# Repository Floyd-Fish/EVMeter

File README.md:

# Overview
An EV(Exposure Value) Meter measures EV parameters for cameras automatically. Also measures the Color Temperature.Designed to simplify MF controls on Digital or Mechanical DSLRs

## Progress

V2.1 has been updated: Basic functions completed, **but bug exists**.  

## Hardware design
Tools: KiCad  
See dir: Hardware/Kicad_project

## Software design

**History Version**

- V1.0
  - Tools: Clion + STM32CubeMx  
  - MCU: STM32F070F6P6  
  - See dir: Software

- V2.0
  - Tools: Clion + STM32CubeMx
  - MCU: STM32F072CBT6
  - See dir: Software

- V2.1
  - Tools: MDK5 + STM32CubeMx
  - MCU: STM32F072CBT6
  - See dir: Software

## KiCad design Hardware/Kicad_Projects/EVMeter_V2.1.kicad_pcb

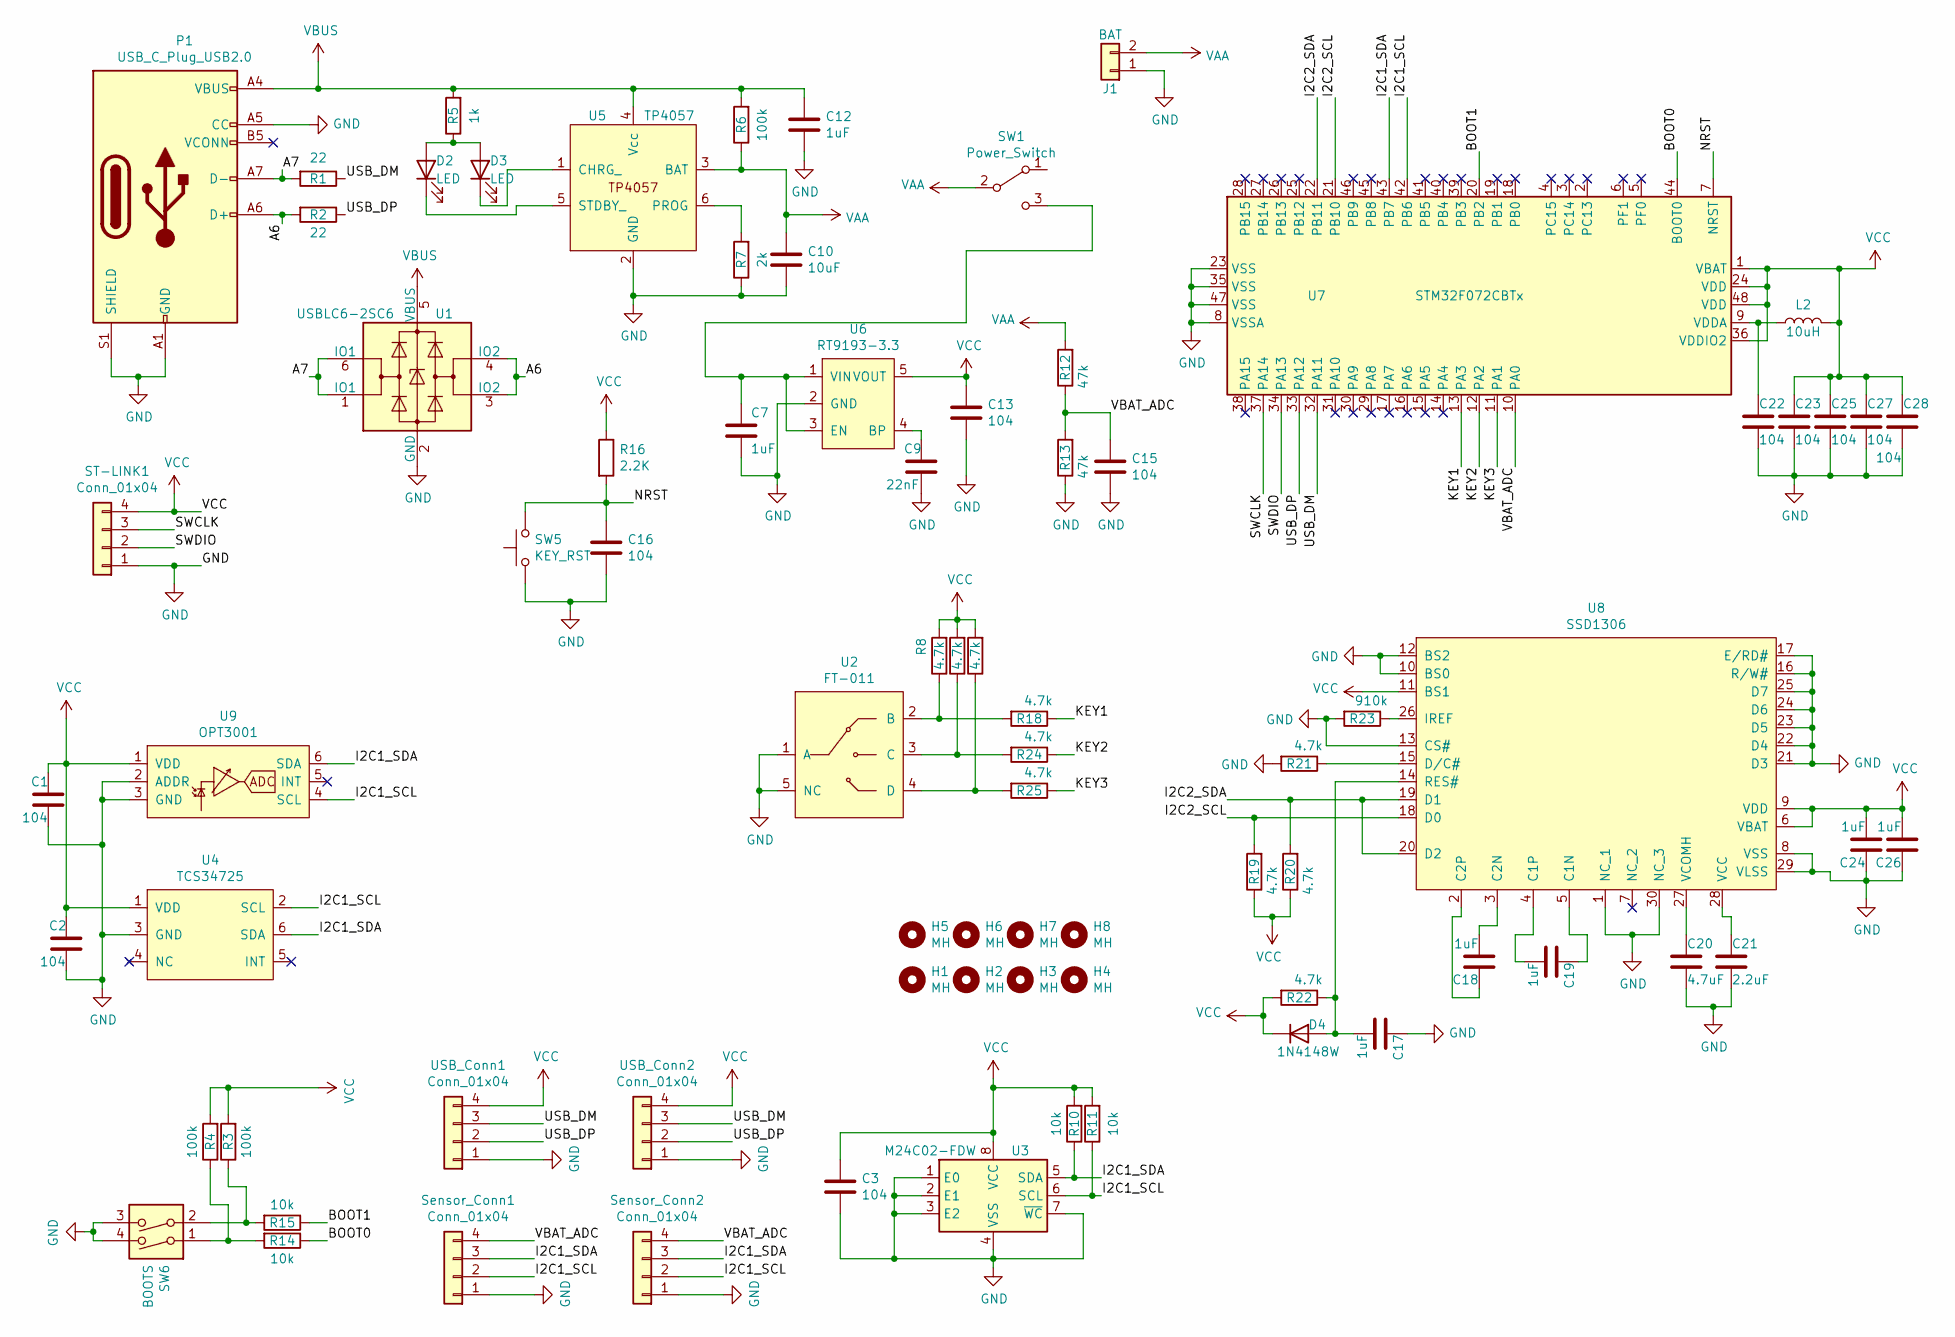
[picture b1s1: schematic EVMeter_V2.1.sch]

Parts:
C1, C2, C3, C13, C15, C16, C22, C23, C25, C27, C28: 104; C_0603_1608Metric
C7, C12, C17, C18, C19, C24, C26: 1uF; C_0603_1608Metric
C9: 22nF; C_0603_1608Metric
C10: 10uF; C_0805_2012Metric
C20: 4.7uF; C_0805_2012Metric
C21: 2.2uF; C_0805_2012Metric
D2, D3: LED; LED_0603_1608Metric_Castellated
D4: 1N4148W; D_SOD-323
H1, H2, H3, H4, H5, H6, H7, H8: MH; MountingHole_2.2mm_M2
J1: BAT; PinSocket_1x02_P2.00mm_Vertical
L2: 10uH; L_0805_2012Metric_Pad1.15x1.40mm_HandSolder
P1: USB_C_Plug_USB2.0; USB_C_Receptacle_HRO_TYPE-C-31-M-12
R1, R2: 22; R_0603_1608Metric
R3, R4, R6: 100k; R_0603_1608Metric
R5: 1k; R_0603_1608Metric
R7: 2k; R_0603_1608Metric
R8, R9, R17, R18, R19, R20, R21, R22, R24, R25: 4.7k; R_0603_1608Metric
R10, R11, R14, R15: 10k; R_0603_1608Metric
R12, R13: 47k; R_0603_1608Metric
R16: 2.2K; R_0603_1608Metric
R23: 910k; R_0603_1608Metric
ST-LINK1: Conn_01x04; Molex_PicoBlade_53261-0471_1x04-1MP_P1.25mm_Horizontal
SW1: Power_Switch; SW_SPDT_CK-JS102011SAQN
SW5: KEY_RST; Panasonic_EVQPUL_EVQPUC
SW6: BOOTS; SW_DIP_SPSTx02_Slide_Yourcee_W5.40mm_P1.27mm
Sensor_Conn1: Conn_01x04; PinHeader_1x04_P2.54mm_Vertical
Sensor_Conn2: Conn_01x04; PinSocket_1x04_P2.54mm_Vertical
U1: USBLC6-2SC6; SOT-23-6
U2: FT-011
U3: M24C02-FDW; SOIC-8_3.9x4.9mm_P1.27mm
U4: TCS34725; TSL2591_DFN6
U5: TP4057; SOT-23-6
U6: RT9193-3.3; SOT-23-5
U7: STM32F072CBTx; LQFP-48_7x7mm_P0.5mm
U8: SSD1306; SSD1306-12864_Alter
U9: OPT3001; USON-6
USB_Conn1: Conn_01x04; PinHeader_1x04_P2.54mm_Vertical
USB_Conn2: Conn_01x04; PinSocket_1x04_P2.54mm_Vertical

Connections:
/A6: P1.A6 (D+), R2.2, U1.3 (IO2), U1.4 (IO2)
/A7: P1.A7 (D-), R1.2, U1.1 (IO1), U1.6 (IO1)
/BOOT0: R14.1, U7.44 (BOOT0)
/BOOT1: R15.1, U7.20 (PB2)
/I2C1_SCL: R11.1, Sensor_Conn1.2, Sensor_Conn2.2, U3.6 (SCL), U4.2 (SCL), U7.42 (PB6), U9.4 (SCL)
/I2C1_SDA: R10.1, Sensor_Conn1.3, Sensor_Conn2.3, U3.5 (SDA), U4.6 (SDA), U7.43 (PB7), U9.6 (SDA)
/I2C2_SCL: R19.2, U7.21 (PB10), U8.18 (D0)
/I2C2_SDA: R20.2, U7.22 (PB11), U8.19 (D1), U8.20 (D2)
/KEY1: R18.1, U7.13 (PA3)
/KEY2: R24.1, U7.12 (PA2)
/KEY3: R25.1, U7.11 (PA1)
/NRST: C16.1, R16.2, SW5.2, U7.7 (NRST)
/SWCLK: ST-LINK1.3, U7.37 (PA14)
/SWDIO: ST-LINK1.2, U7.34 (PA13)
/USB_DM: R1.1, U7.32 (PA11), USB_Conn1.3, USB_Conn2.3
/USB_DP: R2.1, U7.33 (PA12), USB_Conn1.2, USB_Conn2.2
/VBAT_ADC: C15.1, R12.1, R13.2, Sensor_Conn1.4, Sensor_Conn2.4, U7.10 (PA0)
GND: C1.2, C2.2, C3.2, C7.2, C9.2, C10.2, C12.2, C13.2, C15.2, C16.2, C17.1, C20.2, C21.2, C22.2, C23.2, C24.1, C25.2, C26.1, C27.2, C28.2, J1.1, P1.A1 (GND), P1.A5 (CC), P1.A12 (GND), P1.B1 (GND), P1.B12 (GND), P1.S1 (SHIELD), R7.1, R13.1, R21.2, R23.2, ST-LINK1.1, SW5.1, SW6.3, SW6.4, Sensor_Conn1.1, Sensor_Conn2.1, U1.2 (GND), U2.1 (A), U2.5 (NC), U3.1 (E0), U3.2 (E1), U3.3 (E2), U3.4 (VSS), U3.7 (~WC), U4.3 (GND), U5.2 (GND), U6.2 (GND), U7.8 (VSSA), U7.23 (VSS), U7.35 (VSS), U7.47 (VSS), U8.1 (NC_1), U8.8 (VSS), U8.10 (BS0), U8.12 (BS2), U8.13 (CS#), U8.16 (R/W#), U8.17 (E/RD#), U8.21 (D3), U8.22 (D4), U8.23 (D5), U8.24 (D6), U8.25 (D7), U8.29 (VLSS), U8.30 (NC_3), U9.2 (ADDR), U9.3 (GND), USB_Conn1.1, USB_Conn2.1
unnamed: C7.1, SW1.3 (C), U6.1 (VIN), U6.3 (EN)
unnamed: C9.1, U6.4 (BP)
unnamed: C17.2, D4.2 (A), R22.1, U8.14 (RES#)
unnamed: C18.1, U8.2 (C2P)
unnamed: C18.2, U8.3 (C2N)
unnamed: C19.1, U8.5 (C1N)
unnamed: C19.2, U8.4 (C1P)
unnamed: C20.1, U8.27 (VCOMH)
unnamed: C21.1, U8.28 (VCC)
unnamed: C22.1, L2.1, U7.9 (VDDA)
unnamed: D2.1 (K), U5.5 (STDBY_)
unnamed: D2.2 (A), D3.2 (A), R5.1
unnamed: D3.1 (K), U5.1 (CHRG_)
unnamed: R7.2, U5.6 (PROG)
unnamed: R4.1, R14.2, SW6.1
unnamed: R3.1, R15.2, SW6.2
unnamed: R17.1, R25.2, U2.4 (D)
unnamed: R8.1, R18.2, U2.2 (B)
unnamed: R21.1, U8.15 (D/C#)
unnamed: R23.1, U8.26 (IREF)
unnamed: R9.1, R24.2, U2.3 (C)
VAA: C10.1, J1.2, R6.1, R12.2, SW1.2 (B), U5.3 (BAT)
VBUS: C12.1, P1.A4 (VBUS), P1.A9 (VBUS), P1.B4 (VBUS), P1.B9 (VBUS), R5.2, R6.2, U1.5 (VBUS), U5.4 (Vcc)
VCC: C1.1, C2.1, C3.1, C13.1, C23.1, C24.2, C25.1, C26.2, C27.1, C28.1, D4.1 (K), L2.2, R3.2, R4.2, R8.2, R9.2, R10.2, R11.2, R16.1, R17.2, R19.1, R20.1, R22.2, ST-LINK1.4, U3.8 (VCC), U4.1 (VDD), U6.5 (VOUT), U7.1 (VBAT), U7.24 (VDD), U7.36 (VDDIO2), U7.48 (VDD), U8.6 (VBAT), U8.9 (VDD), U8.11 (BS1), U9.1 (VDD), USB_Conn1.4, USB_Conn2.4

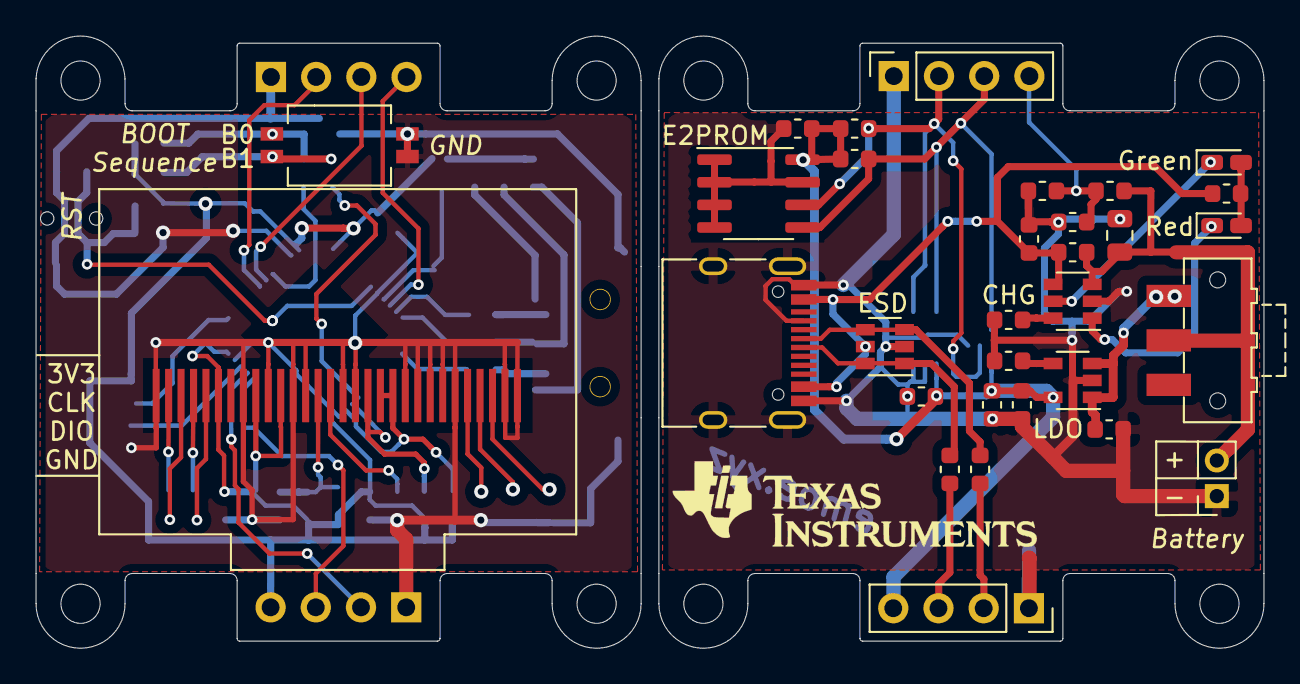
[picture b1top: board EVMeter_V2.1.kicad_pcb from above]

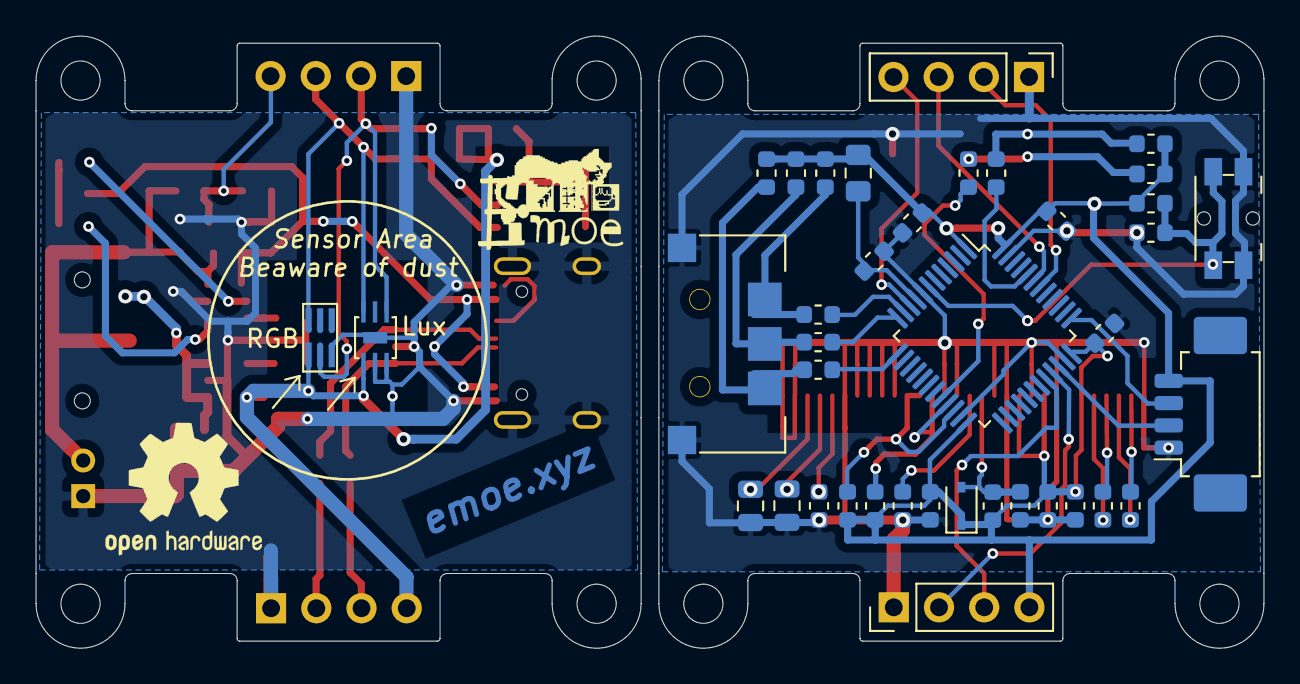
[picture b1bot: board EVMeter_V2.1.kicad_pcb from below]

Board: 2 copper layers, 69.0 x 34.4 mm, 78 parts (39 on the bottom side), 42 nets.

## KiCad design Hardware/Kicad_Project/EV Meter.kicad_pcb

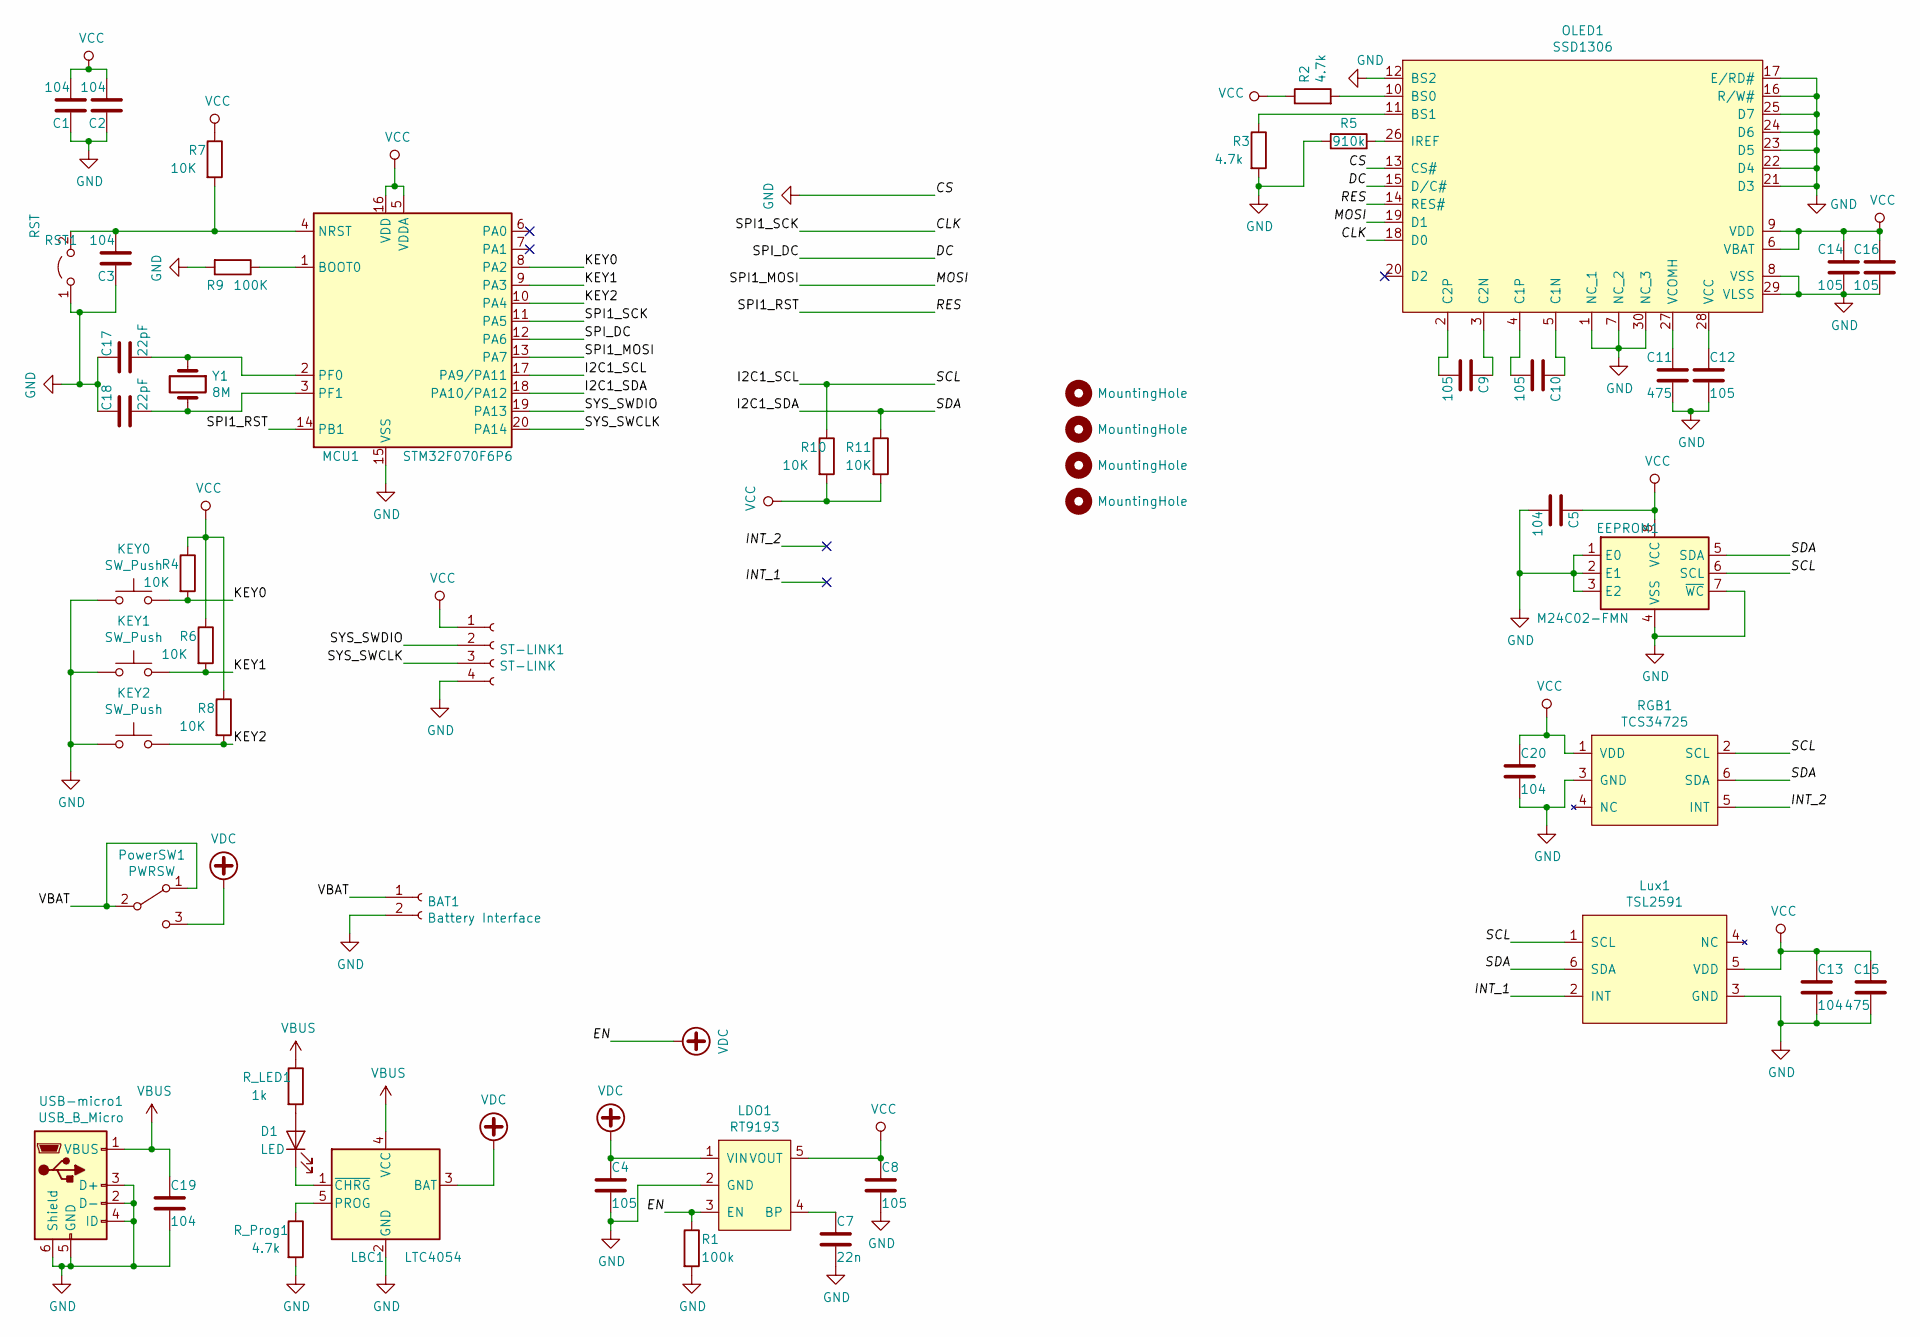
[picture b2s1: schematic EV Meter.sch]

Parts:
BAT1: Battery Interface; PinSocket_1x02_P2.54mm_Vertical
C1, C2, C3, C5, C13, C19, C20: 104; C_0603_1608Metric
C4, C8, C9, C10, C12, C14, C16: 105; C_0603_1608Metric
C7: 22n; C_0603_1608Metric
C11, C15: 475; C_0805_2012Metric
C17, C18: 22pF; C_0603_1608Metric
D1: LED; LED_0603_1608Metric
EEPROM1: M24C02-FMN; SOIC-8_3.9x4.9mm_P1.27mm
H1, H2, H3, H4: MountingHole; MountingHole_2.2mm_M2_DIN965
KEY0, KEY1, KEY2: SW_Push; SW_SPST_TL3305C
LBC1: LTC4054; SOT-23-5
LDO1: RT9193; SOT-23-5
Lux1: TSL2591; TSL2591_DFN6
MCU1: STM32F070F6P6; TSSOP-20_4.4x6.5mm_P0.65mm
OLED1: SSD1306; SSD1306-12864
PowerSW1: PWRSW; SW_SPDT_CK-JS102011SAQN
R1: 100k; R_0603_1608Metric
R2, R3: 4.7k; R_0603_1608Metric
R4, R6, R7, R8, R10, R11: 10K; R_0603_1608Metric
R5: 910k; R_0603_1608Metric
R9: 100K; R_0603_1608Metric
RGB1: TCS34725; TSL2591_DFN6
RST1: RST; SolderJumper-2_P1.3mm_Open_RoundedPad1.0x1.5mm
R_LED1: 1k; R_0603_1608Metric
R_Prog1: 4.7k; R_0603_1608Metric
ST-LINK1: ST-LINK; PinHeader_1x04_P2.54mm_Vertical
USB-micro1: USB_B_Micro; USB_Micro-B_Wuerth_629105150521
Y1: 8M; Crystal_SMD_5032-2Pin_5.0x3.2mm

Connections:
/CLK: MCU1.11 (PA5), OLED1.18 (D0)
/DC: MCU1.12 (PA6), OLED1.15 (D/C#)
/I2C1_SCL: EEPROM1.6 (SCL), Lux1.1 (SCL), MCU1.17 (PA9/PA11), R10.1, RGB1.2 (SCL)
/I2C1_SDA: EEPROM1.5 (SDA), Lux1.6 (SDA), MCU1.18 (PA10/PA12), R11.1, RGB1.6 (SDA)
/INT_1: Lux1.2 (INT)
/INT_2: RGB1.5 (INT)
/KEY0: KEY0.2, MCU1.8 (PA2), R4.2
/KEY1: KEY1.2, MCU1.9 (PA3), R6.2
/KEY2: KEY2.2, MCU1.10 (PA4), R8.2
/MOSI: MCU1.13 (PA7), OLED1.19 (D1)
/RES: MCU1.14 (PB1), OLED1.14 (RES#)
/SYS_SWCLK: MCU1.20 (PA14), ST-LINK1.3
/SYS_SWDIO: MCU1.19 (PA13), ST-LINK1.2
/VBAT: BAT1.1, PowerSW1.1 (A), PowerSW1.2 (B)
GND: BAT1.2, C1.1, C2.1, C3.1, C4.2, C5.2, C7.2, C8.2, C11.2, C12.2, C13.2, C14.2, C15.2, C16.2, C17.1, C18.1, C19.2, C20.2, EEPROM1.1 (E0), EEPROM1.2 (E1), EEPROM1.3 (E2), EEPROM1.4 (VSS), EEPROM1.7 (~WC), KEY0.1, KEY1.1, KEY2.1, LBC1.2 (GND), LDO1.2 (GND), Lux1.3 (GND), MCU1.15 (VSS), OLED1.1 (NC_1), OLED1.7 (NC_2), OLED1.8 (VSS), OLED1.12 (BS2), OLED1.13 (CS#), OLED1.16 (R/W#), OLED1.17 (E/RD#), OLED1.21 (D3), OLED1.22 (D4), OLED1.23 (D5), OLED1.24 (D6), OLED1.25 (D7), OLED1.29 (VLSS), OLED1.30 (NC_3), R1.2, R3.2, R5.2, R9.2, RGB1.3 (GND), RST1.1 (A), R_Prog1.2, ST-LINK1.4, USB-micro1.2 (D-), USB-micro1.3 (D+), USB-micro1.4 (ID), USB-micro1.5 (GND), USB-micro1.6 (Shield)
unnamed: C3.2, MCU1.4 (NRST), R7.2, RST1.2 (B)
unnamed: C7.1, LDO1.4 (BP)
unnamed: C9.1, OLED1.3 (C2N)
unnamed: C9.2, OLED1.2 (C2P)
unnamed: C10.1, OLED1.5 (C1N)
unnamed: C10.2, OLED1.4 (C1P)
unnamed: C11.1, OLED1.27 (VCOMH)
unnamed: C12.1, OLED1.28 (VCC)
unnamed: C17.2, MCU1.2 (PF0), Y1.1
unnamed: C18.2, MCU1.3 (PF1), Y1.2
unnamed: D1.1 (K), LBC1.1 (~CHRG)
unnamed: D1.2 (A), R_LED1.2
unnamed: LBC1.5 (PROG), R_Prog1.1
unnamed: MCU1.1 (BOOT0), R9.1
unnamed: OLED1.10 (BS0), R2.2
unnamed: OLED1.11 (BS1), R3.1
unnamed: OLED1.26 (IREF), R5.1
VBUS: C19.1, LBC1.4 (VCC), R_LED1.1, USB-micro1.1 (VBUS)
VCC: C1.2, C2.2, C5.1, C8.1, C13.1, C14.1, C15.1, C16.1, C20.1, EEPROM1.8 (VCC), LDO1.5 (VOUT), Lux1.5 (VDD), MCU1.5 (VDDA), MCU1.16 (VDD), OLED1.6 (VBAT), OLED1.9 (VDD), R2.1, R4.1, R6.1, R7.1, R8.1, R10.2, R11.2, RGB1.1 (VDD), ST-LINK1.1
VDC: C4.1, LBC1.3 (BAT), LDO1.1 (VIN), LDO1.3 (EN), PowerSW1.3 (C), R1.1

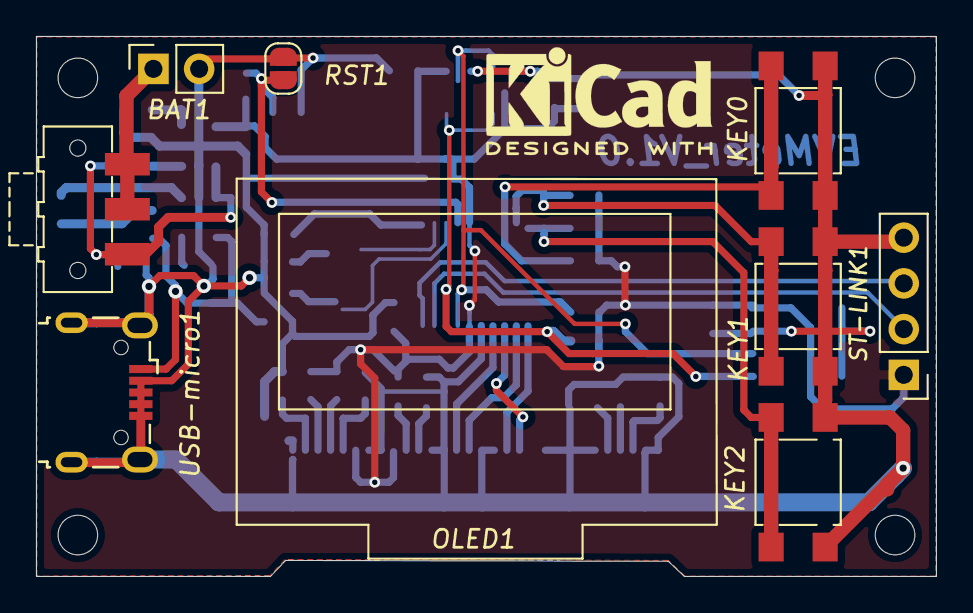
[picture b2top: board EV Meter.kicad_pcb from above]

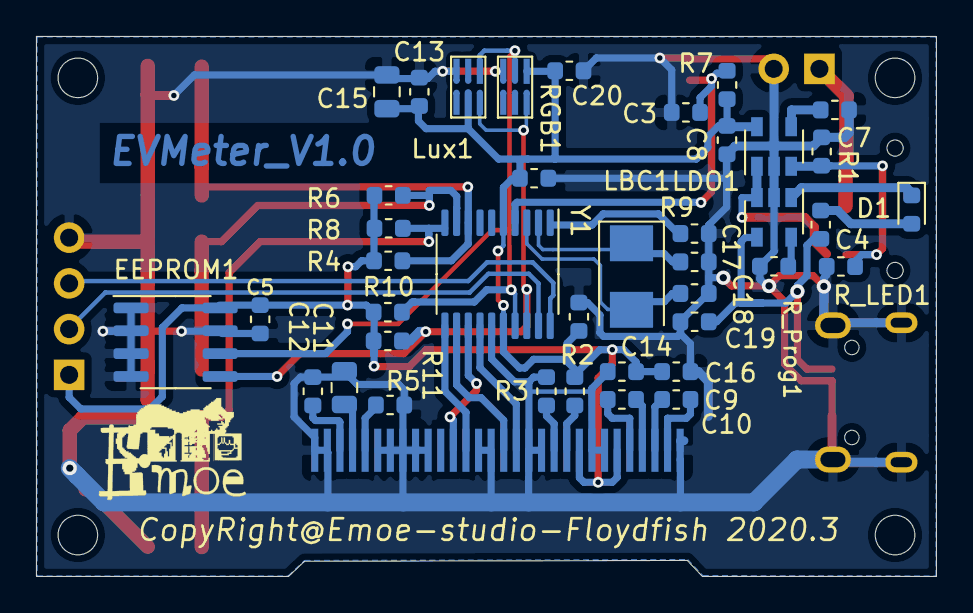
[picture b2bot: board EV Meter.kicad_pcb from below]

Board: 2 copper layers, 50.0 x 30.0 mm, 53 parts (40 on the bottom side), 33 nets.

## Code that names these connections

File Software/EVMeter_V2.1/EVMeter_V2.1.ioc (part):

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Mcu.Name=STM32F072C(8-B)Tx
Mcu.Package=LQFP48
Mcu.UserName=STM32F072CBTx
PA0.Mode=IN0
PA0.Signal=ADC_IN0
PA1.Signal=GPIO_Input
PA11.Mode=Device
PA11.Signal=USB_DM
PA12.Mode=Device
PA12.Signal=USB_DP
PA13.Mode=Serial_Wire
PA13.Signal=SYS_SWDIO
PA14.Mode=Serial_Wire
PA14.Signal=SYS_SWCLK
PA2.Signal=GPIO_Input
PA3.Signal=GPIO_Input
PB10.Mode=I2C
PB10.Signal=I2C2_SCL
PB11.Mode=I2C
PB11.Signal=I2C2_SDA
PB6.Mode=I2C
PB6.Signal=I2C1_SCL
PB7.Mode=I2C
PB7.Signal=I2C1_SDA
PB9.Signal=GPIO_Output
RCC.SYSCLKFreq_VALUE=48000000
RCC.SYSCLKSource=RCC_SYSCLKSOURCE_HSI48
board=custom

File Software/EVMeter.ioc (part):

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Mcu.Name=STM32F070F6Px
Mcu.Package=TSSOP20
Mcu.UserName=STM32F070F6Px
PA10.Mode=I2C
PA10.Signal=I2C1_SDA
PA13.Mode=Serial_Wire
PA13.Signal=SYS_SWDIO
PA14.Mode=Serial_Wire
PA14.Signal=SYS_SWCLK
PA2.Signal=GPIO_Input
PA3.Signal=GPIO_Input
PA4.Signal=GPIO_Input
PA5.Mode=TX_Only_Simplex_Unidirect_Master
PA5.Signal=SPI1_SCK
PA6.Signal=GPIO_Output
PA7.Mode=TX_Only_Simplex_Unidirect_Master
PA7.Signal=SPI1_MOSI
PA9.Mode=I2C
PA9.Signal=I2C1_SCL
PB1.Signal=GPIO_Output
PF0-OSC_IN.Mode=HSE-External-Oscillator
PF0-OSC_IN.Signal=RCC_OSC_IN
PF1-OSC_OUT.Mode=HSE-External-Oscillator
PF1-OSC_OUT.Signal=RCC_OSC_OUT
RCC.SYSCLKFreq_VALUE=48000000
RCC.SYSCLKSource=RCC_SYSCLKSOURCE_PLLCLK
board=custom

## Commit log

2020-03-17 Add initial project frameworks
2020-03-24 Update PCB gerber
2020-03-31 update tcs34725 and ssd1306 lib
2020-06-18 Update Version V2.0's Hardware design
2021-01-16 Update V2.1 Design

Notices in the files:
Hardware/Kicad_Project/EV Meter.kicad_pcb:
CopyRight@Emoe-studio-Floydfish 2020.3
